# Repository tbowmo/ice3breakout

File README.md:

# ICE3breakout

This is a breakout board for atmels jtagice3 debugger. Enabling you to power target via the debug connector,
also adding cortex M debug header, with correct pinout.

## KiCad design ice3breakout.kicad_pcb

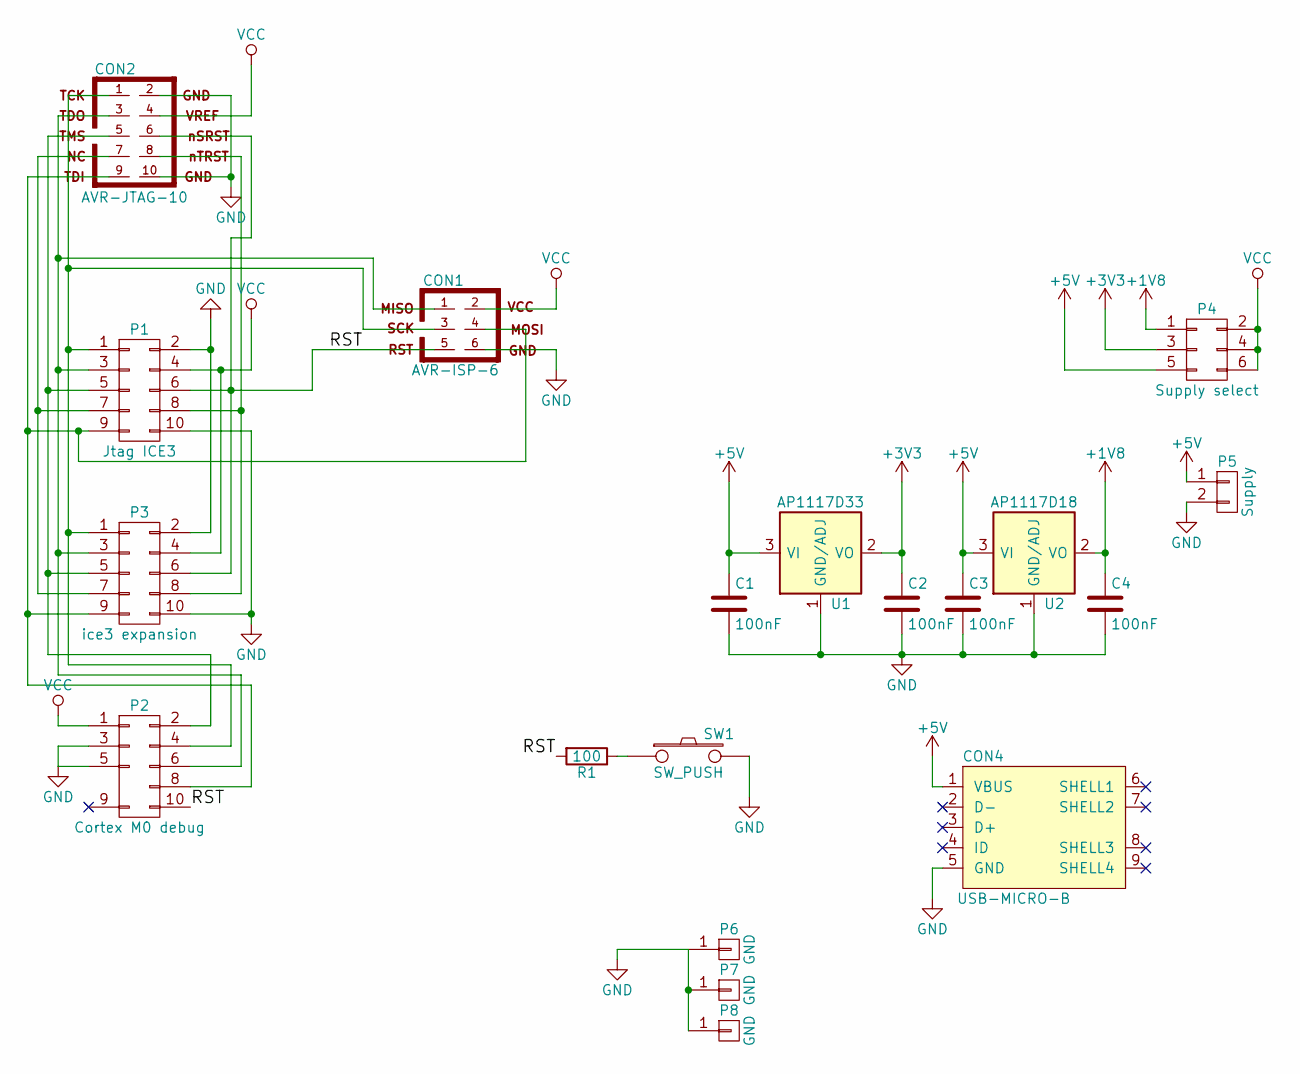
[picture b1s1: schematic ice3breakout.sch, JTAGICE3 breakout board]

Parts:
C1, C2, C3, C4: 100nF; C_0603_HandSoldering
CON1: AVR-ISP-6; vasch_strip_3x2
CON2: AVR-JTAG-10; vasch_strip_5x2
CON4: USB-MICRO-B; Micro_USB
P1: Jtag ICE3; FCI_10P_HDR
P2: Cortex M0 debug; FCI_10P_HDR
P3: ice3 expansion; FCI_10P_HDR
P4: Supply select; Pin_Header_Straight_2x03
P5: Supply; Pin_Header_Straight_1x02
P6, P7, P8: GND; Pin_Header_Straight_1x01
R1: 100; R_0603_HandSoldering
SW1: SW_PUSH; SW_SPST_SMD_J-LEAD_4.3MM
U1: AP1117D33; SOT-223
U2: AP1117D18; SOT-223

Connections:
+1V8: C4.1, P4.1, U2.2 (VO)
+3V3: C2.1, P4.3, U1.2 (VO)
+5V: C1.1, C3.1, CON4.1 (VBUS), P4.5, P5.1, U1.3 (VI), U2.3 (VI)
/RST: CON1.5, CON2.6, P1.6, P2.10, P3.6, R1.2
GND: C1.2, C2.2, C3.2, C4.2, CON1.6, CON2.2, CON2.10, CON4.5 (GND), P1.2, P1.10, P2.3, P2.5, P3.2, P3.10, P5.2, P6.1, P7.1, P8.1, SW1.2, U1.1 (GND/ADJ), U2.1 (GND/ADJ)
unnamed: CON1.1, CON2.3, P1.3, P2.6, P3.3
unnamed: CON1.3, CON2.1, P1.1, P2.4, P3.1
unnamed: CON1.4, CON2.9, P1.9, P2.8, P3.9
unnamed: CON2.5, P1.5, P2.2, P3.5
unnamed: CON2.7, P1.7, P3.7
unnamed: CON2.8, P1.8, P3.8
unnamed: R1.1, SW1.1
VCC: CON1.2, CON2.4, P1.4, P2.1, P3.4, P4.2, P4.4, P4.6

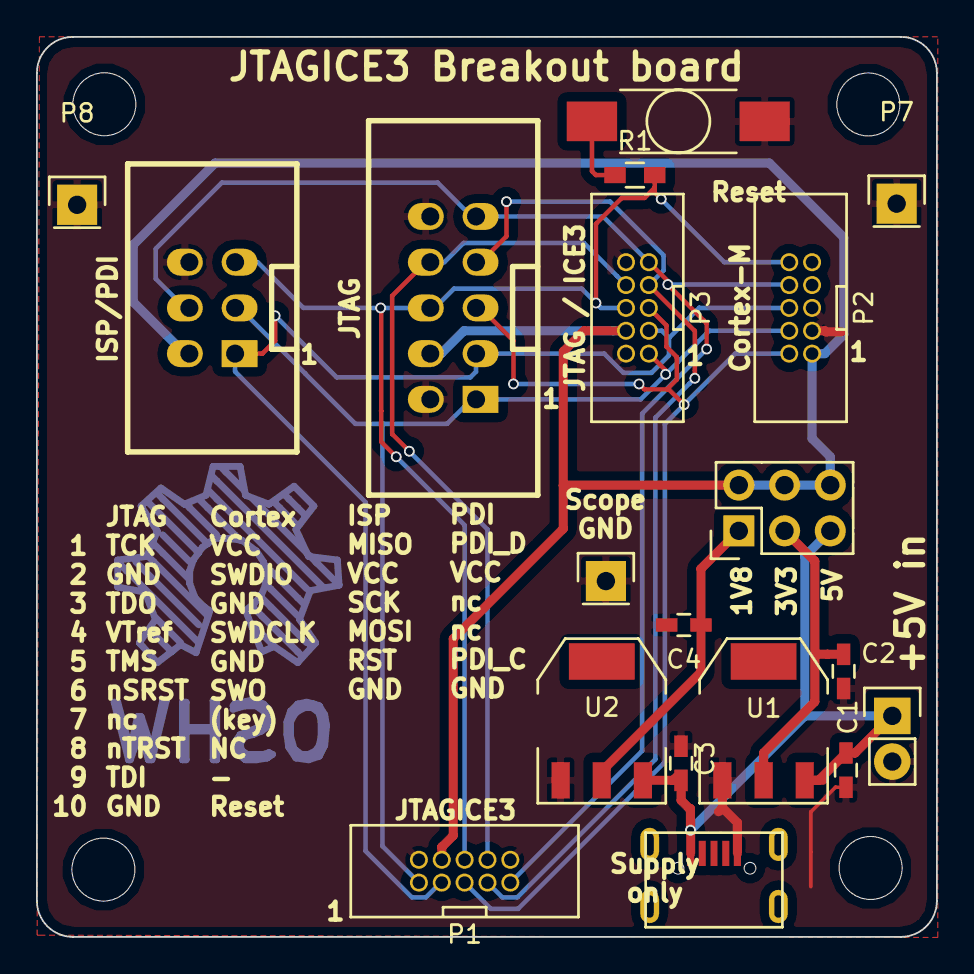
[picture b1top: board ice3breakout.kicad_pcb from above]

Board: 2 copper layers, 50.0 x 50.0 mm, 19 parts (0 on the bottom side), 13 nets.

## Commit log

2015-08-06 Added schematic as pdf, and manufacturing files
2015-08-06 Added pin legend to silkscreen, OSHW logo to bottom layer copper
2015-08-07 closes #1, closes #2, closes #3
2015-08-08 V1 board ready for manufacturing
2017-05-10 Added extra GND pins
2017-05-10 Adds CERN license files
    fixes #4
